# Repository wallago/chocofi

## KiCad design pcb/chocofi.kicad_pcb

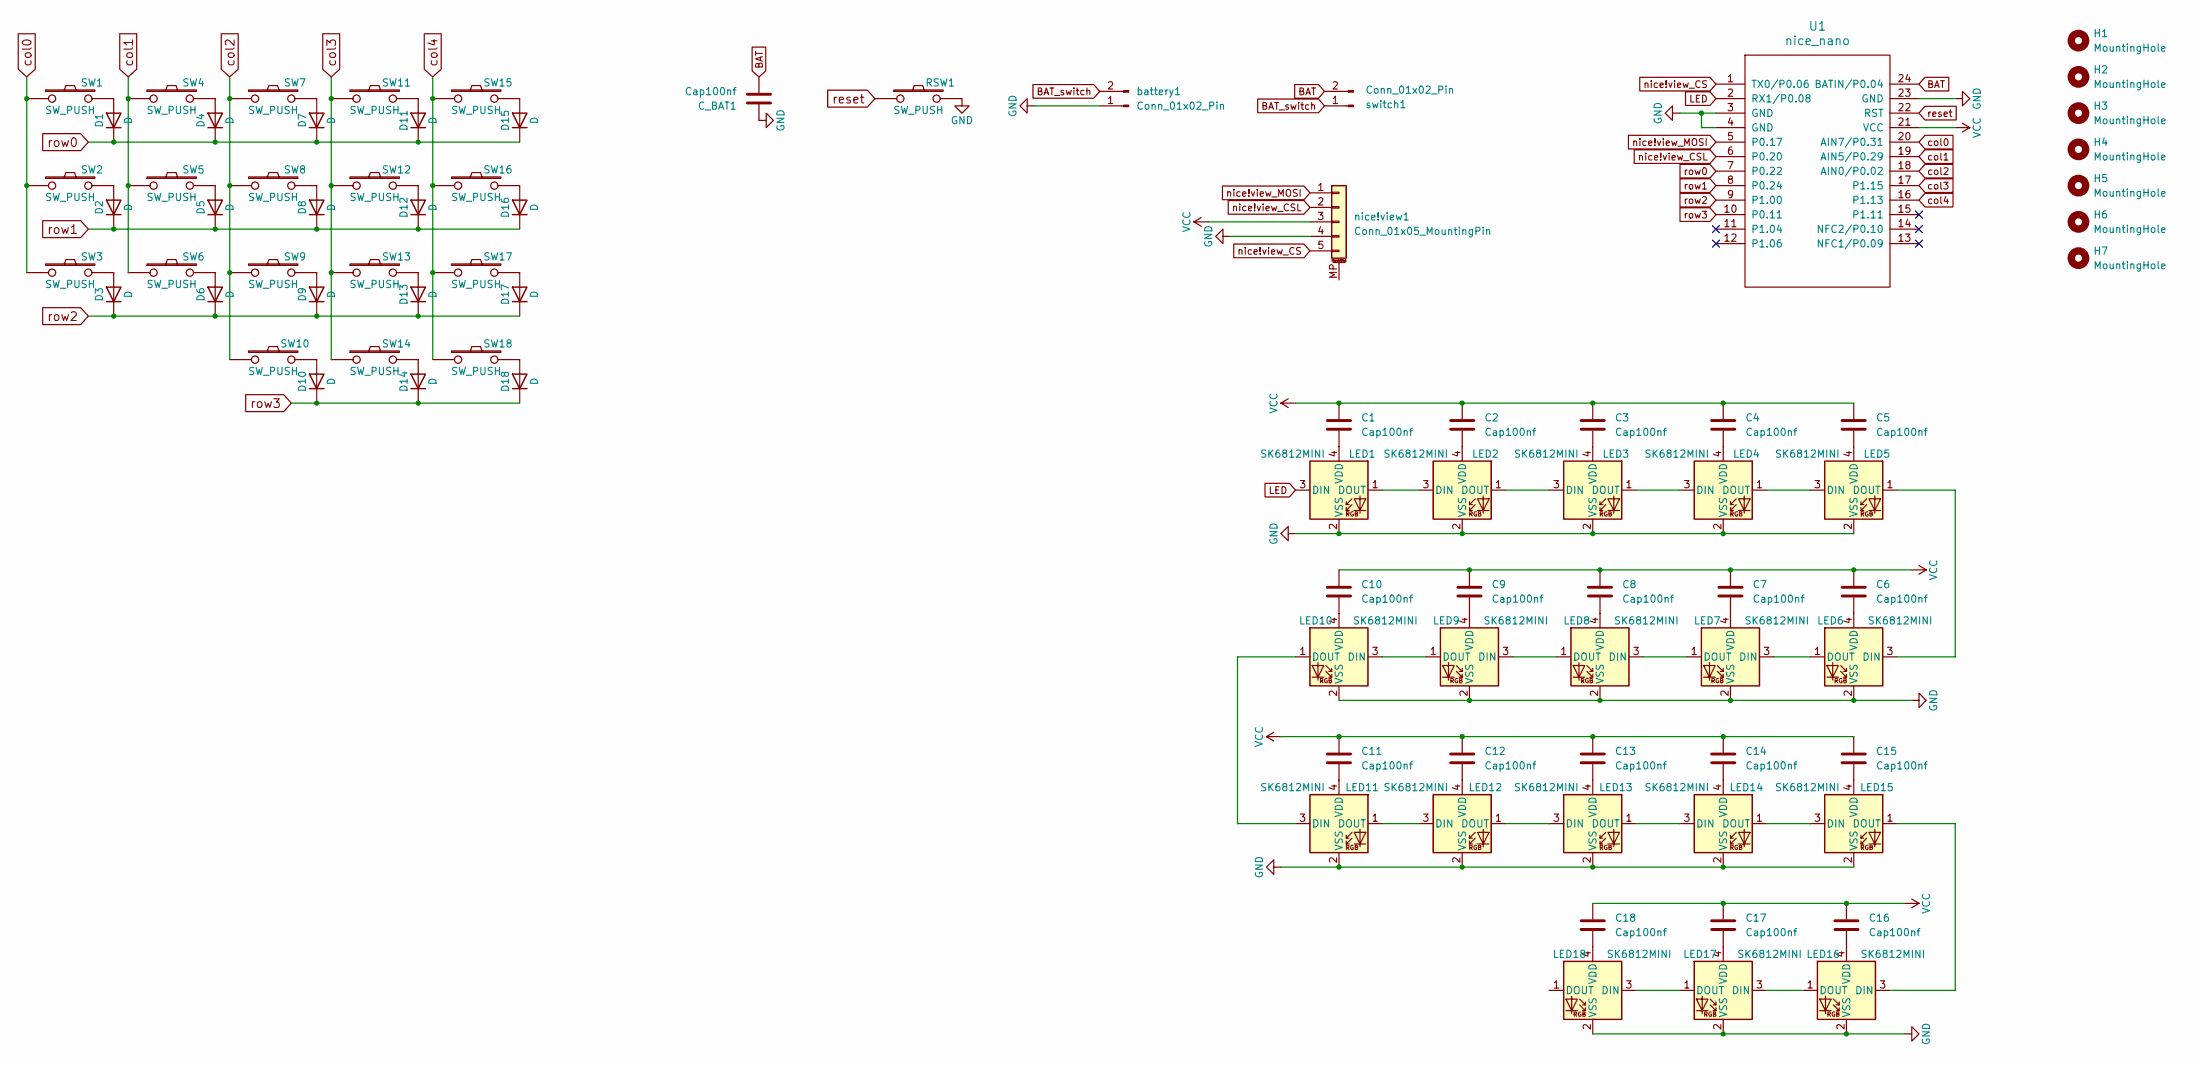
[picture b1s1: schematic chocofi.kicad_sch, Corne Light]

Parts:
C1, C2, C3, C4, C5, C6, C7, C8, C9, C10, C11, C12, C13, C14, C15, C16, C17, C18: Cap100nf; C_0805_2012Metric_Pad1.18x1.45mm_HandSolder
C_BAT1: Cap100nf; C_0805_2012Metric_Pad1.18x1.45mm_HandSolder
D1, D2, D3, D4, D5, D6, D7, D8, D9, D10, D11, D12, D13, D14, D15, D16, D17, D18: D; D_SOD-323_HandSoldering
H1, H2, H3, H4, H5, H6, H7: MountingHole; MountingHole_2.2mm_M2_DIN965_Pad
LED1, LED2, LED3, LED4, LED5, LED6, LED7, LED8, LED9, LED10, LED11, LED12, LED13, LED14, LED15, LED16, LED17, LED18: SK6812MINI; YS-SK6812MINI-E
RSW1: SW_PUSH; SW_SPST_TS-1088-xR020
SW1, SW2, SW3, SW4, SW5, SW6, SW7, SW8, SW9, SW10, SW11, SW12, SW13, SW14, SW15, SW16, SW17, SW18: SW_PUSH; SW_Hotswap_Kailh_Choc_V1V2_Plated
U1: nice_nano
battery1: Conn_01x02_Pin; JST_SH_SM02B-SRSS-TB_1x02-1MP_P1.00mm_Horizontal
nice!view1: Conn_01x05_MountingPin; PinHeader_1x05_P2.54mm_Vertical
switch1: Conn_01x02_Pin; JST_SH_SM02B-SRSS-TB_1x02-1MP_P1.00mm_Horizontal

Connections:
BAT: C_BAT1.2, U1.24 (BATIN/P0.04), switch1.2; also elsewhere on the board
BAT_switch: battery1.2, switch1.1
GND: C_BAT1.1, LED1.2 (VSS), LED2.2 (VSS), LED3.2 (VSS), LED4.2 (VSS), LED5.2 (VSS), LED6.2 (VSS), LED7.2 (VSS), LED8.2 (VSS), LED9.2 (VSS), LED10.2 (VSS), LED11.2 (VSS), LED12.2 (VSS), LED13.2 (VSS), LED14.2 (VSS), LED15.2 (VSS), LED16.2 (VSS), LED17.2 (VSS), LED18.2 (VSS), RSW1.2, U1.3 (GND), U1.4 (GND), U1.23 (GND), battery1.1, nice!view1.4; also elsewhere on the board
LED: LED1.3 (DIN), U1.2 (RX1/P0.08); also elsewhere on the board
unnamed: D1.2 (A), SW1.2
unnamed: D2.2 (A), SW2.2
unnamed: D3.2 (A), SW3.2
unnamed: D4.2 (A), SW4.2
unnamed: D5.2 (A), SW5.2
unnamed: D6.2 (A), SW6.2
unnamed: D7.2 (A), SW7.2
unnamed: D8.2 (A), SW8.2
unnamed: D9.2 (A), SW9.2
unnamed: D10.2 (A), SW10.2
unnamed: D11.2 (A), SW11.2
unnamed: D12.2 (A), SW12.2
unnamed: D13.2 (A), SW13.2
unnamed: D14.2 (A), SW14.2
unnamed: D15.2 (A), SW15.2
unnamed: D16.2 (A), SW16.2
unnamed: D17.2 (A), SW17.2
unnamed: D18.2 (A), SW18.2
unnamed: LED1.1 (DOUT), LED2.3 (DIN)
unnamed: C1.2, LED1.4 (VDD)
unnamed: LED2.1 (DOUT), LED3.3 (DIN)
unnamed: C2.2, LED2.4 (VDD)
unnamed: LED3.1 (DOUT), LED4.3 (DIN)
unnamed: C3.2, LED3.4 (VDD)
unnamed: LED4.1 (DOUT), LED5.3 (DIN)
unnamed: C4.2, LED4.4 (VDD)
unnamed: LED5.1 (DOUT), LED6.3 (DIN)
unnamed: C5.2, LED5.4 (VDD)
unnamed: LED6.1 (DOUT), LED7.3 (DIN)
unnamed: C6.2, LED6.4 (VDD)
unnamed: LED7.1 (DOUT), LED8.3 (DIN)
unnamed: C7.2, LED7.4 (VDD)
unnamed: LED8.1 (DOUT), LED9.3 (DIN)
unnamed: C8.2, LED8.4 (VDD)
unnamed: C9.2, LED9.4 (VDD)
unnamed: LED9.1 (DOUT), LED10.3 (DIN)
unnamed: LED10.1 (DOUT), LED11.3 (DIN)
unnamed: C10.2, LED10.4 (VDD)
unnamed: LED11.1 (DOUT), LED12.3 (DIN)
unnamed: C11.2, LED11.4 (VDD)
unnamed: LED12.1 (DOUT), LED13.3 (DIN)
unnamed: C12.2, LED12.4 (VDD)
unnamed: LED13.1 (DOUT), LED14.3 (DIN)
unnamed: C13.2, LED13.4 (VDD)
unnamed: LED14.1 (DOUT), LED15.3 (DIN)
unnamed: C14.2, LED14.4 (VDD)
unnamed: LED15.1 (DOUT), LED16.3 (DIN)
unnamed: C15.2, LED15.4 (VDD)
unnamed: LED16.1 (DOUT), LED17.3 (DIN)
unnamed: C16.2, LED16.4 (VDD)
unnamed: LED17.1 (DOUT), LED18.3 (DIN)
unnamed: C17.2, LED17.4 (VDD)
unnamed: C18.2, LED18.4 (VDD)
VCC: C1.1, C2.1, C3.1, C4.1, C5.1, C6.1, C7.1, C8.1, C9.1, C10.1, C11.1, C12.1, C13.1, C14.1, C15.1, C16.1, C17.1, C18.1, U1.21 (VCC), nice!view1.3; also elsewhere on the board
col0: SW1.1, SW2.1, SW3.1, U1.20 (AIN7/P0.31); also elsewhere on the board
col1: SW4.1, SW5.1, SW6.1, U1.19 (AIN5/P0.29); also elsewhere on the board
col2: SW7.1, SW8.1, SW9.1, SW10.1, U1.18 (AIN0/P0.02); also elsewhere on the board
col3: SW11.1, SW12.1, SW13.1, SW14.1, U1.17 (P1.15); also elsewhere on the board
col4: SW15.1, SW16.1, SW17.1, SW18.1, U1.16 (P1.13); also elsewhere on the board
nice!view_CS: U1.1 (TX0/P0.06), nice!view1.5; also elsewhere on the board
nice!view_CSL: U1.6 (P0.20), nice!view1.2; also elsewhere on the board
nice!view_MOSI: U1.5 (P0.17), nice!view1.1; also elsewhere on the board
reset: RSW1.1, U1.22 (RST); also elsewhere on the board
row0: D1.1 (K), D4.1 (K), D7.1 (K), D11.1 (K), D15.1 (K), U1.7 (P0.22); also elsewhere on the board
row1: D2.1 (K), D5.1 (K), D8.1 (K), D12.1 (K), D16.1 (K), U1.8 (P0.24); also elsewhere on the board
row2: D3.1 (K), D6.1 (K), D9.1 (K), D13.1 (K), D17.1 (K), U1.9 (P1.00); also elsewhere on the board
row3: D10.1 (K), D14.1 (K), D18.1 (K), U1.10 (P0.11); also elsewhere on the board

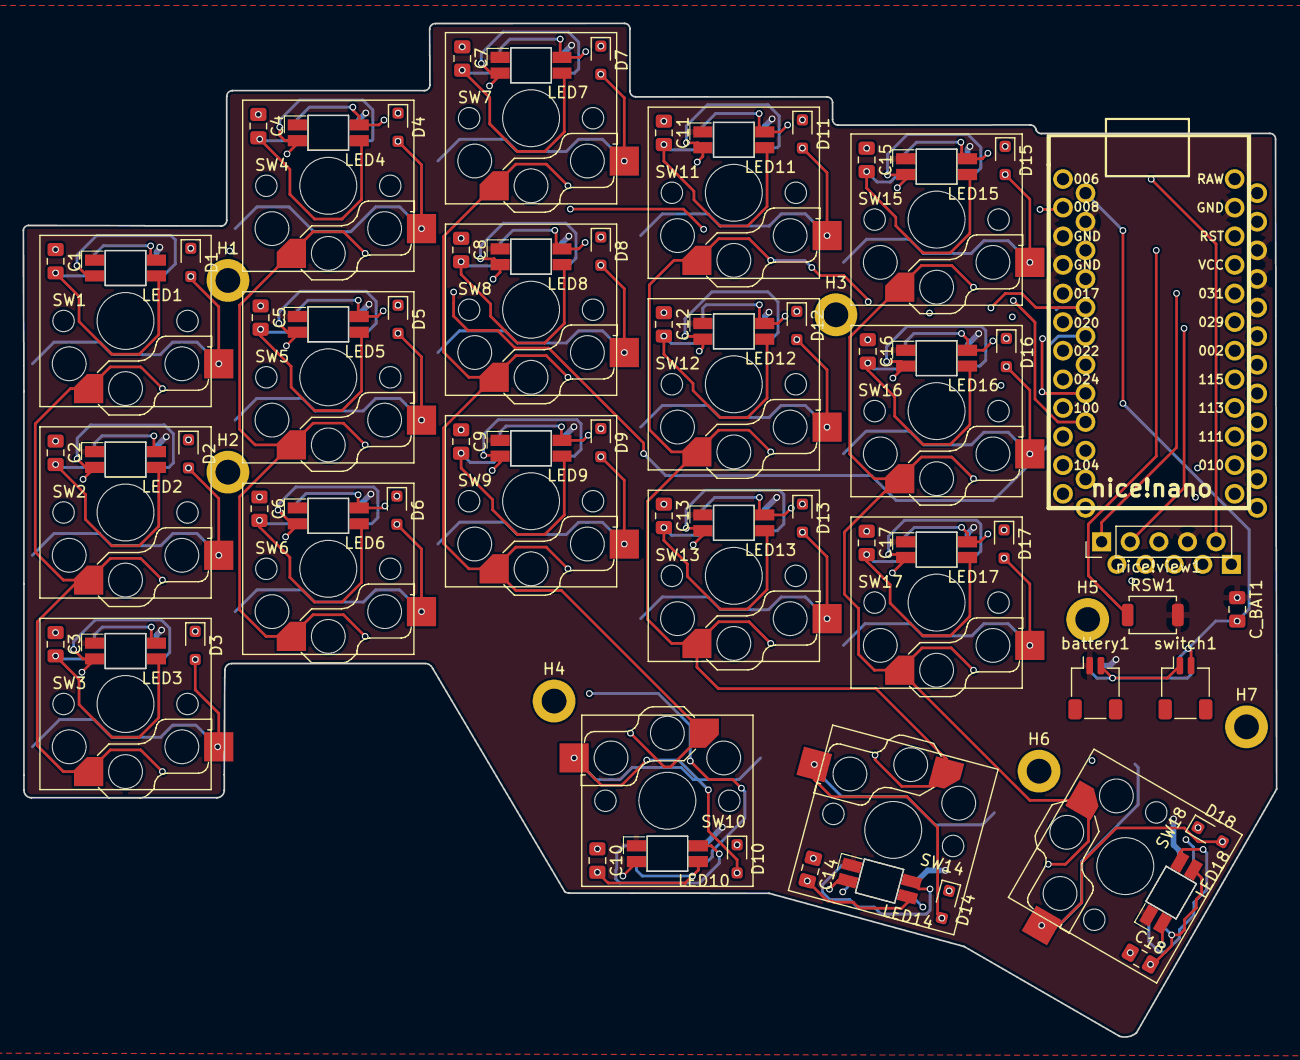
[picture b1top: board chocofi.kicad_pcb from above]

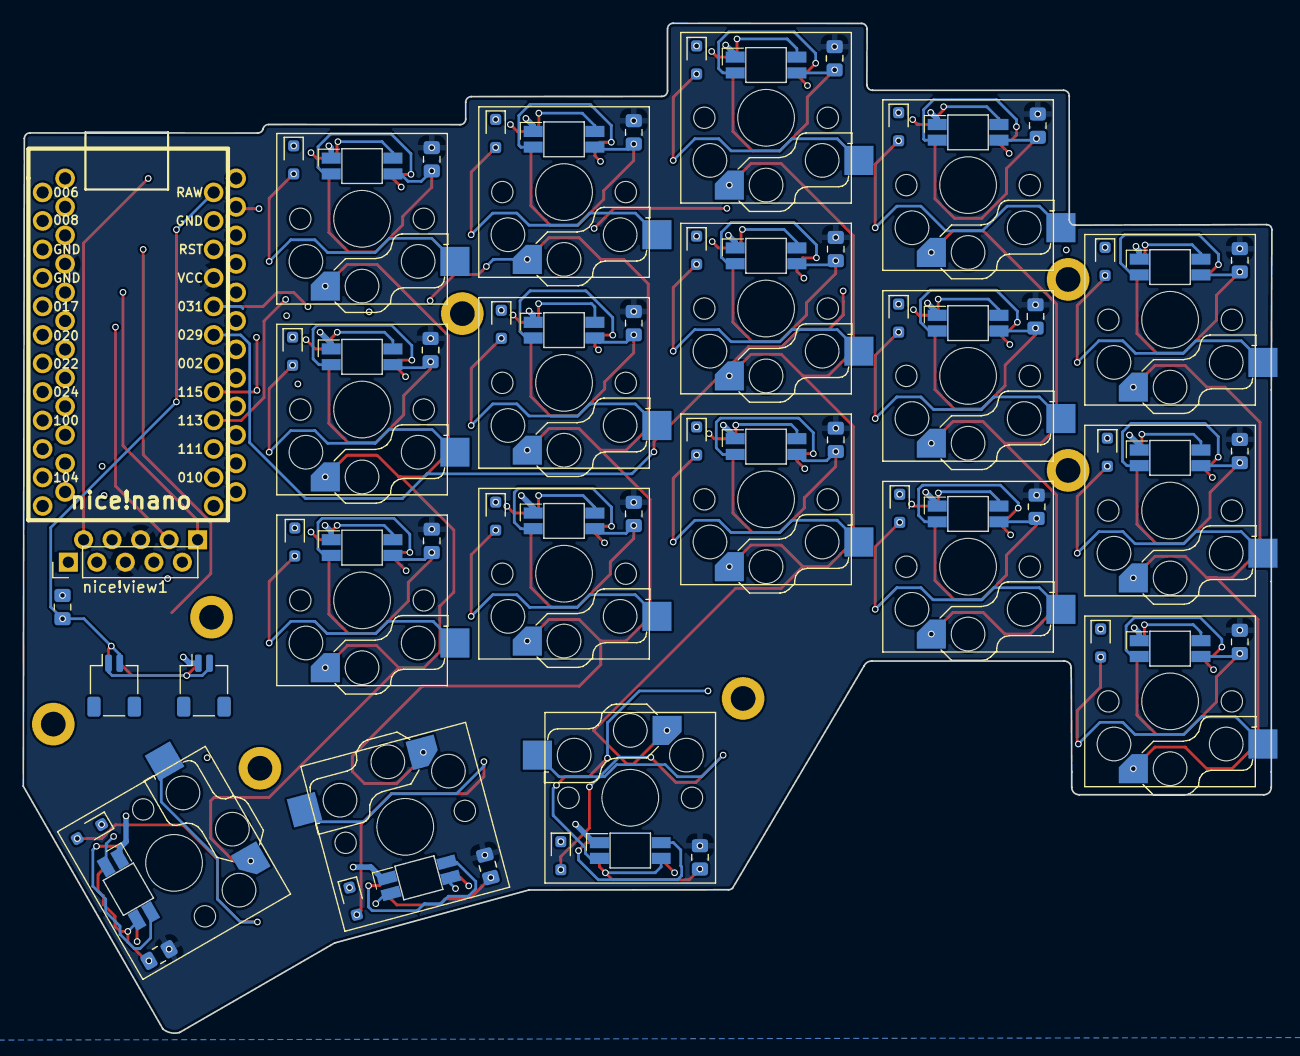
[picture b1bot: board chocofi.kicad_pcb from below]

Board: 4 copper layers, 111.3 x 90.0 mm, 87 parts (2 on the bottom side), 71 nets.

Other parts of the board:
U1#2: nice_nano
nice!view1#2: Conn_01x05_MountingPin; PinHeader_1x05_P2.54mm_Vertical

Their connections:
BAT: U1#2.24 (BATIN/P0.04); also elsewhere on the board
GND: U1#2.3 (GND), U1#2.4 (GND), U1#2.23 (GND), nice!view1#2.4; also elsewhere on the board
LED: U1#2.2 (RX1/P0.08); also elsewhere on the board
VCC: U1#2.21 (VCC), nice!view1#2.3; also elsewhere on the board
col0: U1#2.20 (AIN7/P0.31); also elsewhere on the board
col1: U1#2.19 (AIN5/P0.29); also elsewhere on the board
col2: U1#2.18 (AIN0/P0.02); also elsewhere on the board
col3: U1#2.17 (P1.15); also elsewhere on the board
col4: U1#2.16 (P1.13); also elsewhere on the board
nice!view_CS: U1#2.1 (TX0/P0.06), nice!view1#2.5; also elsewhere on the board
nice!view_CSL: U1#2.6 (P0.20), nice!view1#2.2; also elsewhere on the board
nice!view_MOSI: U1#2.5 (P0.17), nice!view1#2.1; also elsewhere on the board
reset: U1#2.22 (RST); also elsewhere on the board
row0: U1#2.7 (P0.22); also elsewhere on the board
row1: U1#2.8 (P0.24); also elsewhere on the board
row2: U1#2.9 (P1.00); also elsewhere on the board
row3: U1#2.10 (P0.11); also elsewhere on the board

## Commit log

2026-01-03 feat: init pcb
2026-01-08 feat: update
2026-01-08 feat: cilose
2026-01-09 feat: wip1
2026-02-03 feat(zmk): add zmk setup
2026-02-03 fix(github/actions): fix dir
2026-02-03 wip: test
2026-02-03 wip: testtt
2026-02-03 wip: 1
2026-02-03 fix(zmk): wrong gpio
2026-02-03 wip: ve
2026-02-03 wip: without nice view
2026-02-03 wip: cleanup
2026-02-03 wip: pq
2026-02-03 wip: tq
2026-02-03 wip: reverse
2026-02-03 wip: tqt
2026-02-03 wip: changes
2026-02-04 wip: pinout
2026-02-04 wip: change pinout
2026-02-04 wip: changes pinout
2026-02-04 wip: ie
2026-02-04 wip: xx
2026-02-04 feat(pcb): update it
2026-02-04 wip: update name
2026-02-04 feat(zmk): add studio
2026-02-09 feat(zmk): make it work
2026-02-11 feat(case): add case py
2026-02-12 wip(case): update it
2026-02-14 feat: init
2026-02-15 feat(case): improving
2026-02-15 feat(nix): add a freecad tips update
2026-02-15 feat(gitignore): add python cache
2026-02-15 feat(gitignor): add python cache
2026-02-16 feat(case): add components
2026-02-17 feat(pcb/schematic): update footprint for switch + nice!view socket
2026-02-17 feat(zmk): add led support
2026-02-17 feat(pcb/schematic): update LED handling
2026-02-17 wip(pcb): update it
2026-02-17 feat(pcb): upgrade
2026-02-18 feat(pcb): have a good version
2026-02-18 feat(pcb): update for aisler
